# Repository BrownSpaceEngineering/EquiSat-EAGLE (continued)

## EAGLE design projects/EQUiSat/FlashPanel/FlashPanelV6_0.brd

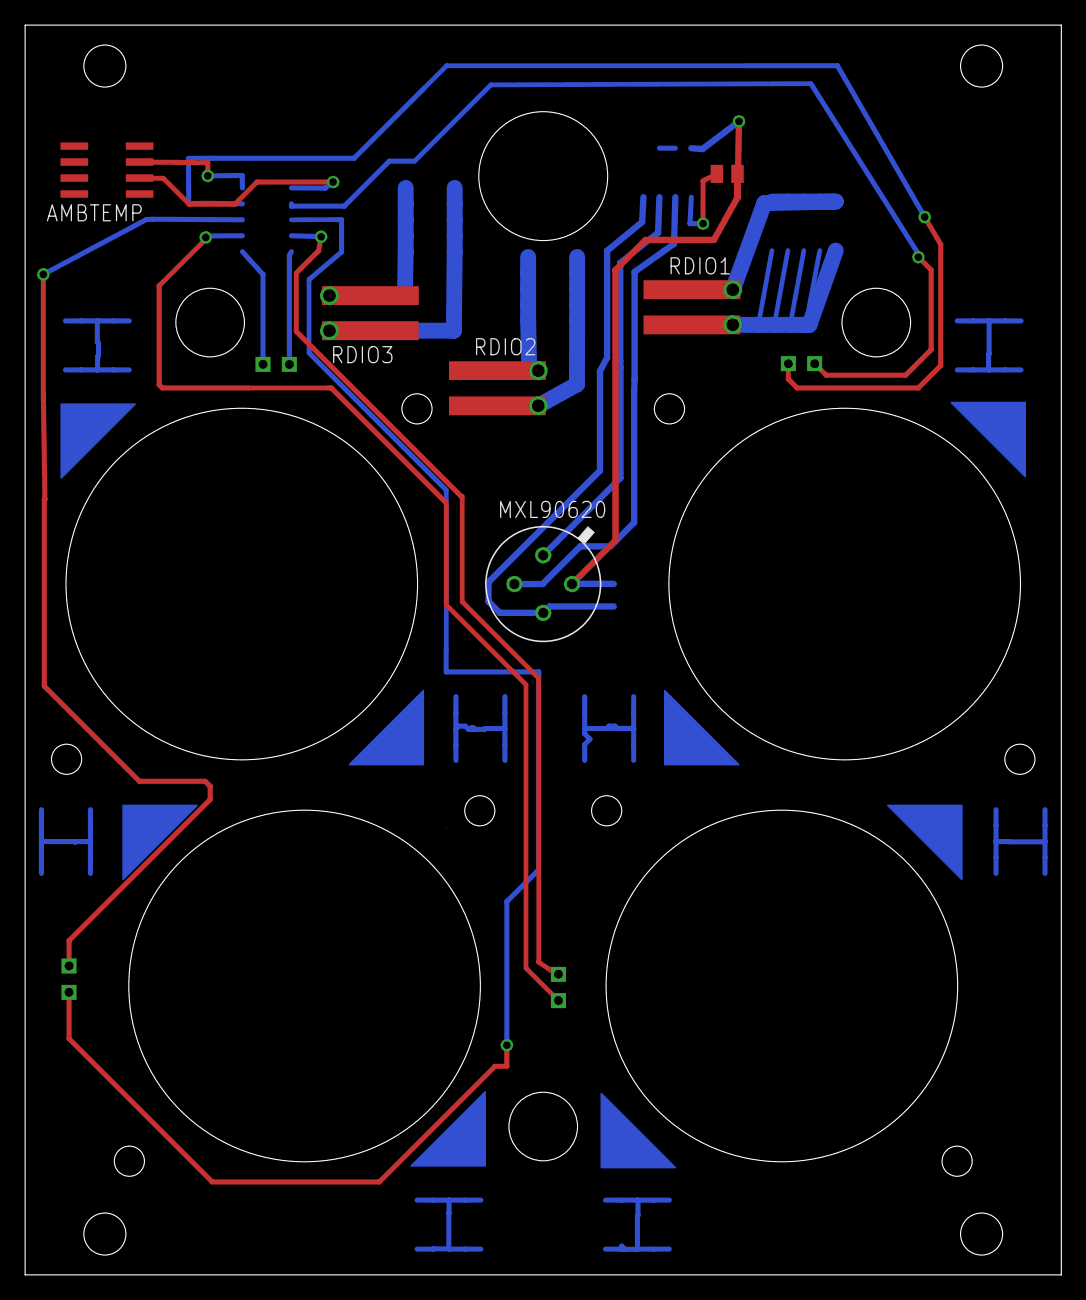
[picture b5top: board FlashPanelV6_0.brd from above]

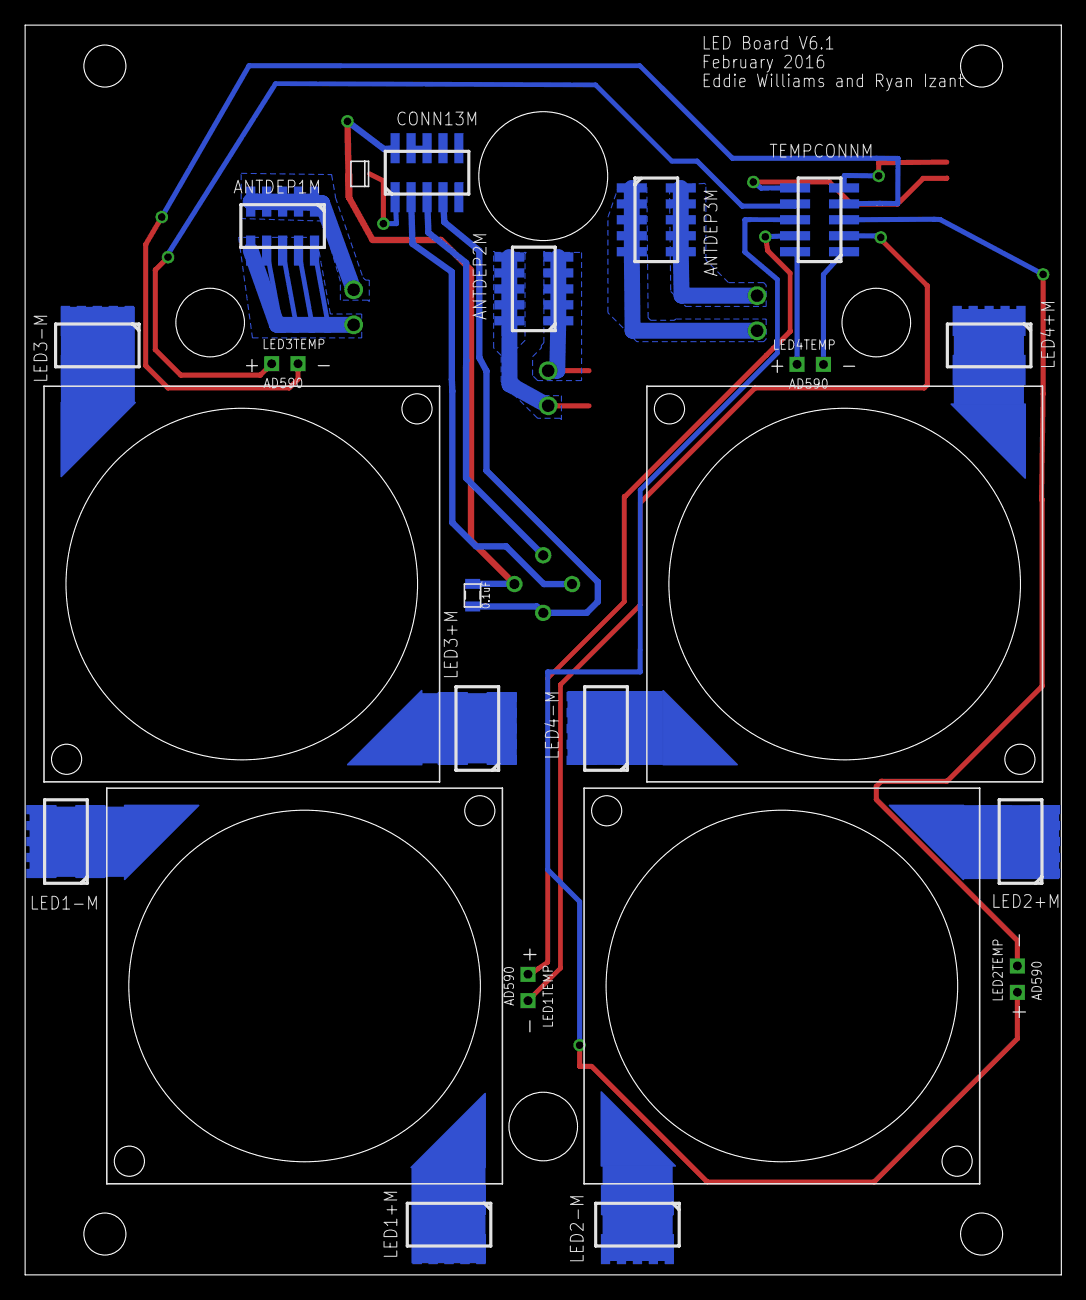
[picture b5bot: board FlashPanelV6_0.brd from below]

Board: 2 copper layers, 82.5 x 99.5 mm, 28 parts (26 on the bottom side), 30 nets.

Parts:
AMBTEMP: AD590; 8SOIC
ANTDEP1M, ANTDEP2M, ANTDEP3M: 10PINMALE
C1: 0.1uF; 0805
CONN13M: 10PINMALE
LED1, LED2, LED3, LED4: CXM27
LED1+M, LED1-M, LED2+M, LED2-M, LED3+M, LED3-M, LED4+M, LED4-M: 10PINMALE
LED1TEMP, LED2TEMP, LED3TEMP, LED4TEMP: AD590-TH; AD590TH
RDIO1, RDIO2, RDIO3: RDIO; RDIO_DPLY
TEMPCONNM: 10PINMALE
U$1: MXL90620
U$2: PHOTODETECTBOTTOM

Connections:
3V3: C1.2, CONN13M.P4, U$1.VDD
GND: C1.1, CONN13M.P10, U$1.VSS, U$2.GND
unnamed: LED3.ANODE, LED3+M.P1, LED3+M.P2, LED3+M.P3, LED3+M.P4, LED3+M.P5, LED3+M.P6, LED3+M.P7, LED3+M.P8, LED3+M.P9, LED3+M.P10
unnamed: LED3.CATHODE, LED3-M.P1, LED3-M.P2, LED3-M.P3, LED3-M.P4, LED3-M.P5, LED3-M.P6, LED3-M.P7, LED3-M.P8, LED3-M.P9, LED3-M.P10
unnamed: LED2.CATHODE, LED2+M.P1, LED2+M.P2, LED2+M.P3, LED2+M.P4, LED2+M.P5, LED2+M.P6, LED2+M.P7, LED2+M.P8, LED2+M.P9, LED2+M.P10
unnamed: LED2.ANODE, LED2-M.P1, LED2-M.P2, LED2-M.P3, LED2-M.P4, LED2-M.P5, LED2-M.P6, LED2-M.P7, LED2-M.P8, LED2-M.P9, LED2-M.P10
unnamed: LED1.CATHODE, LED1+M.P1, LED1+M.P2, LED1+M.P3, LED1+M.P4, LED1+M.P5, LED1+M.P6, LED1+M.P7, LED1+M.P8, LED1+M.P9, LED1+M.P10
unnamed: LED1.ANODE, LED1-M.P1, LED1-M.P2, LED1-M.P3, LED1-M.P4, LED1-M.P5, LED1-M.P6, LED1-M.P7, LED1-M.P8, LED1-M.P9, LED1-M.P10
unnamed: LED4.CATHODE, LED4-M.P1, LED4-M.P2, LED4-M.P3, LED4-M.P4, LED4-M.P5, LED4-M.P6, LED4-M.P7, LED4-M.P8, LED4-M.P9, LED4-M.P10
unnamed: LED4.ANODE, LED4+M.P1, LED4+M.P2, LED4+M.P3, LED4+M.P4, LED4+M.P5, LED4+M.P6, LED4+M.P7, LED4+M.P8, LED4+M.P9, LED4+M.P10
unnamed: ANTDEP1M.P1, ANTDEP1M.P2, ANTDEP1M.P3, ANTDEP1M.P4, ANTDEP1M.P5, RDIO1.P3, RDIO1.P4
unnamed: ANTDEP2M.P6, ANTDEP2M.P7, ANTDEP2M.P8, ANTDEP2M.P9, ANTDEP2M.P10, RDIO2.P1, RDIO2.P2
unnamed: ANTDEP2M.P1, ANTDEP2M.P2, ANTDEP2M.P3, ANTDEP2M.P4, ANTDEP2M.P5, RDIO2.P3, RDIO2.P4
unnamed: ANTDEP3M.P6, ANTDEP3M.P7, ANTDEP3M.P8, ANTDEP3M.P9, ANTDEP3M.P10, RDIO3.P1, RDIO3.P2
unnamed: ANTDEP3M.P1, ANTDEP3M.P2, ANTDEP3M.P3, ANTDEP3M.P4, ANTDEP3M.P5, RDIO3.P3, RDIO3.P4
unnamed: LED4TEMP.P$2, TEMPCONNM.P1
unnamed: LED1TEMP.P$2, TEMPCONNM.P2
unnamed: LED2TEMP.P$2, TEMPCONNM.P3
unnamed: LED3TEMP.P$2, TEMPCONNM.P4
unnamed: LED4TEMP.P$1, TEMPCONNM.P10
unnamed: LED1TEMP.P$1, TEMPCONNM.P9
unnamed: LED2TEMP.P$1, TEMPCONNM.P8
unnamed: LED3TEMP.P$1, TEMPCONNM.P7
unnamed: AMBTEMP.3, TEMPCONNM.P5
unnamed: AMBTEMP.2, TEMPCONNM.P6
PDOUT: CONN13M.P1, U$2.PWROUT
RDIO1: ANTDEP1M.P6, ANTDEP1M.P7, ANTDEP1M.P8, ANTDEP1M.P9, ANTDEP1M.P10, RDIO1.P1, RDIO1.P2
SCL: CONN13M.P3, U$1.SCL
SDA: CONN13M.P2, U$1.SDA
TEST: CONN13M.P8, CONN13M.P9

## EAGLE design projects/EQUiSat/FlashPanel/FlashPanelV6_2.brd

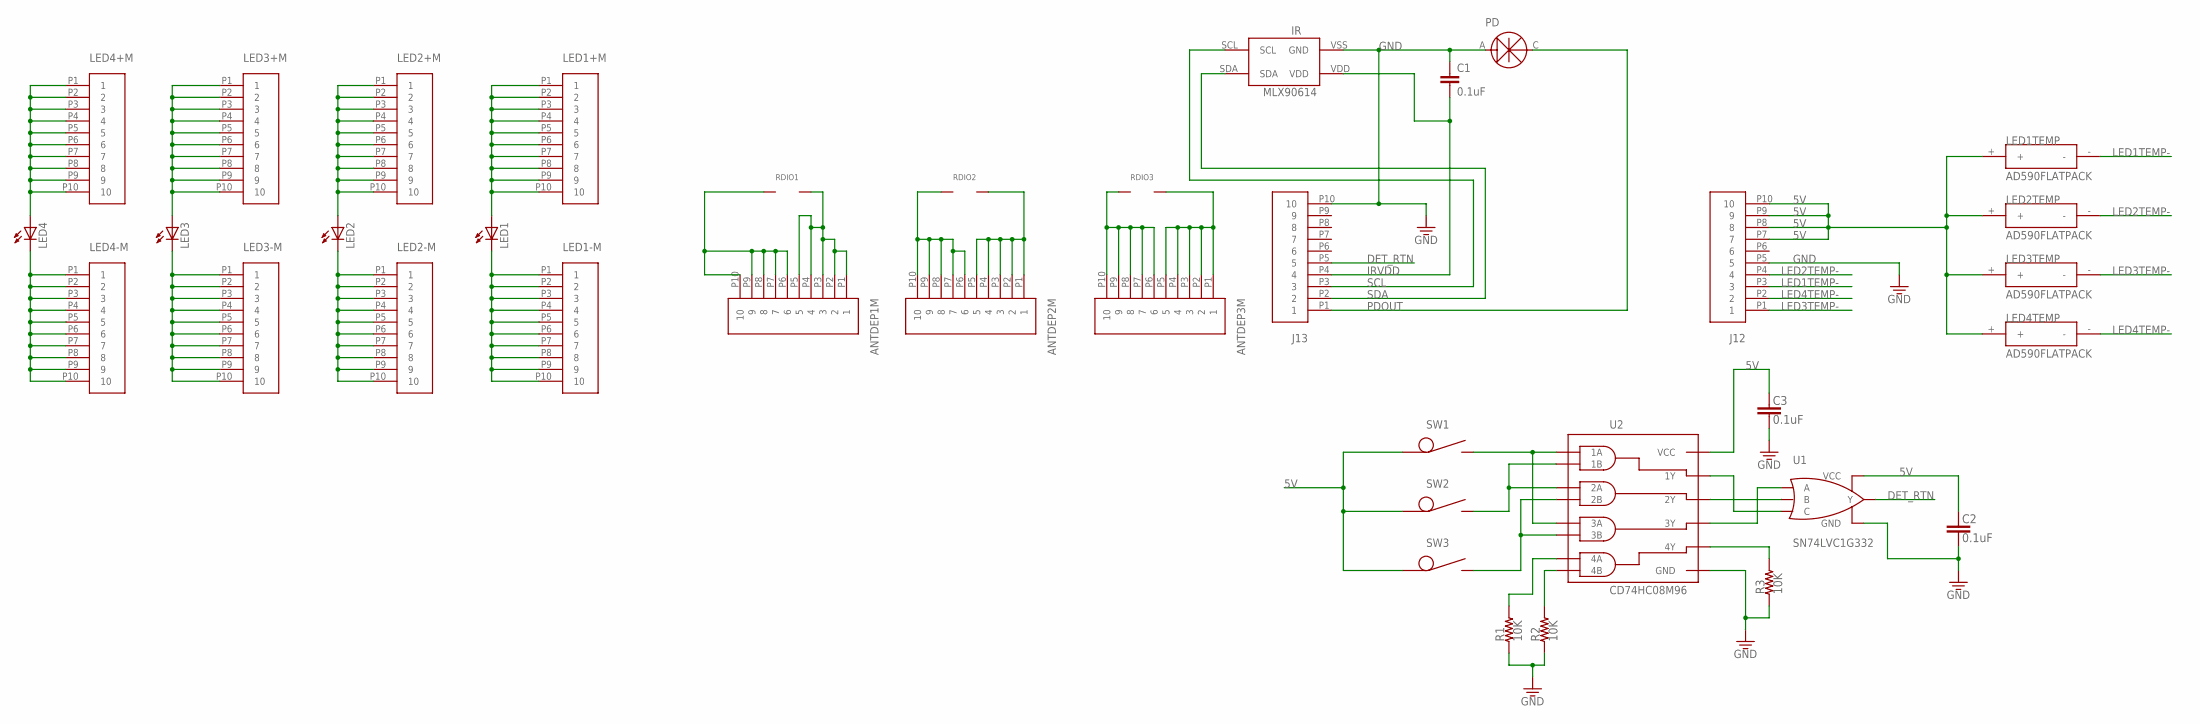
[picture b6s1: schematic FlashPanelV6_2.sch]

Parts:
ANTDEP1M, ANTDEP2M, ANTDEP3M: 10PINMALE
C1, C2, C3: 0.1uF; 0805
IR: MXL90614; MXL90620
J12, J13: 10PINMALE
LED1, LED2, LED3, LED4: CXM27
LED1+M, LED1-M, LED2+M, LED2-M, LED3+M, LED3-M, LED4+M, LED4-M: 10PINMALE
LED1TEMP, LED2TEMP, LED3TEMP, LED4TEMP: AD590FLATPACK; FLATPACK
PD: TEMD6200
R1, R2, R3: 10K; 0805
RDIO1, RDIO2, RDIO3: RDIO; RDIO_DPLY
SW1, SW2, SW3: SW-DETECT; SW-SPRING
U1: SN74LVC1G332; DCK-6
U2: CD74HC08M96; SOIC-14

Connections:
5V: C2.1, C3.1, J12.P7 (7), J12.P8 (8), J12.P9 (9), J12.P10 (10), LED1TEMP.+, LED2TEMP.+, LED3TEMP.+, LED4TEMP.+, SW1.P$1, SW2.P$1, SW3.P$1, U1.P$5 (VCC), U2.P$14 (VCC)
DET_RTN: J13.P5 (5), U1.P$4 (Y)
GND: C1.1, C2.2, C3.2, IR.VSS (GND), J12.P5 (5), J13.P10 (10), PD.A, R1.1, R2.1, R3.1, U1.P$2 (GND), U2.P$7 (GND)
IRVDD: C1.2, IR.VDD, J13.P4 (4)
LED1M: LED1.CATHODE (C), LED1-M.P1 (1), LED1-M.P2 (2), LED1-M.P3 (3), LED1-M.P4 (4), LED1-M.P5 (5), LED1-M.P6 (6), LED1-M.P7 (7), LED1-M.P8 (8), LED1-M.P9 (9), LED1-M.P10 (10)
LED1P: LED1.ANODE (A), LED1+M.P1 (1), LED1+M.P2 (2), LED1+M.P3 (3), LED1+M.P4 (4), LED1+M.P5 (5), LED1+M.P6 (6), LED1+M.P7 (7), LED1+M.P8 (8), LED1+M.P9 (9), LED1+M.P10 (10)
LED1TEMP-: J12.P3 (3), LED1TEMP.-
LED2M: LED2.CATHODE (C), LED2-M.P1 (1), LED2-M.P2 (2), LED2-M.P3 (3), LED2-M.P4 (4), LED2-M.P5 (5), LED2-M.P6 (6), LED2-M.P7 (7), LED2-M.P8 (8), LED2-M.P9 (9), LED2-M.P10 (10)
LED2P: LED2.ANODE (A), LED2+M.P1 (1), LED2+M.P2 (2), LED2+M.P3 (3), LED2+M.P4 (4), LED2+M.P5 (5), LED2+M.P6 (6), LED2+M.P7 (7), LED2+M.P8 (8), LED2+M.P9 (9), LED2+M.P10 (10)
LED2TEMP-: J12.P4 (4), LED2TEMP.-
LED3M: LED3.CATHODE (C), LED3-M.P1 (1), LED3-M.P2 (2), LED3-M.P3 (3), LED3-M.P4 (4), LED3-M.P5 (5), LED3-M.P6 (6), LED3-M.P7 (7), LED3-M.P8 (8), LED3-M.P9 (9), LED3-M.P10 (10)
LED3P: LED3.ANODE (A), LED3+M.P1 (1), LED3+M.P2 (2), LED3+M.P3 (3), LED3+M.P4 (4), LED3+M.P5 (5), LED3+M.P6 (6), LED3+M.P7 (7), LED3+M.P8 (8), LED3+M.P9 (9), LED3+M.P10 (10)
LED3TEMP-: J12.P1 (1), LED3TEMP.-
LED4M: LED4.CATHODE (C), LED4-M.P1 (1), LED4-M.P2 (2), LED4-M.P3 (3), LED4-M.P4 (4), LED4-M.P5 (5), LED4-M.P6 (6), LED4-M.P7 (7), LED4-M.P8 (8), LED4-M.P9 (9), LED4-M.P10 (10)
LED4P: LED4.ANODE (A), LED4+M.P1 (1), LED4+M.P2 (2), LED4+M.P3 (3), LED4+M.P4 (4), LED4+M.P5 (5), LED4+M.P6 (6), LED4+M.P7 (7), LED4+M.P8 (8), LED4+M.P9 (9), LED4+M.P10 (10)
LED4TEMP-: J12.P2 (2), LED4TEMP.-
unnamed: U1.P$6 (C), U2.P$3 (1Y)
unnamed: U1.P$3 (B), U2.P$6 (2Y)
unnamed: U1.P$1 (A), U2.P$8 (3Y)
unnamed: SW1.P$2, U2.P$1 (1A), U2.P$9 (3A)
unnamed: SW2.P$2, U2.P$2 (1B), U2.P$4 (2A)
unnamed: SW3.P$2, U2.P$5 (2B), U2.P$10 (3B)
unnamed: R2.2, U2.P$13 (4B)
unnamed: R1.2, U2.P$12 (4A)
unnamed: R3.2, U2.P$11 (4Y)
PDOUT: J13.P1 (1), PD.C
RDIO1+: ANTDEP1M.P6 (6), ANTDEP1M.P7 (7), ANTDEP1M.P8 (8), ANTDEP1M.P9 (9), ANTDEP1M.P10 (10), RDIO1.P3, RDIO1.P4
RDIO1-: ANTDEP1M.P1 (1), ANTDEP1M.P2 (2), ANTDEP1M.P3 (3), ANTDEP1M.P4 (4), ANTDEP1M.P5 (5), RDIO1.P1, RDIO1.P2
RDIO2+: ANTDEP2M.P6 (6), ANTDEP2M.P7 (7), ANTDEP2M.P8 (8), ANTDEP2M.P9 (9), ANTDEP2M.P10 (10), RDIO2.P3, RDIO2.P4
RDIO2-: ANTDEP2M.P1 (1), ANTDEP2M.P2 (2), ANTDEP2M.P3 (3), ANTDEP2M.P4 (4), ANTDEP2M.P5 (5), RDIO2.P1, RDIO2.P2
RDIO3+: ANTDEP3M.P6 (6), ANTDEP3M.P7 (7), ANTDEP3M.P8 (8), ANTDEP3M.P9 (9), ANTDEP3M.P10 (10), RDIO3.P3, RDIO3.P4
RDIO3-: ANTDEP3M.P1 (1), ANTDEP3M.P2 (2), ANTDEP3M.P3 (3), ANTDEP3M.P4 (4), ANTDEP3M.P5 (5), RDIO3.P1, RDIO3.P2
SCL: IR.SCL, J13.P3 (3)
SDA: IR.SDA, J13.P2 (2)

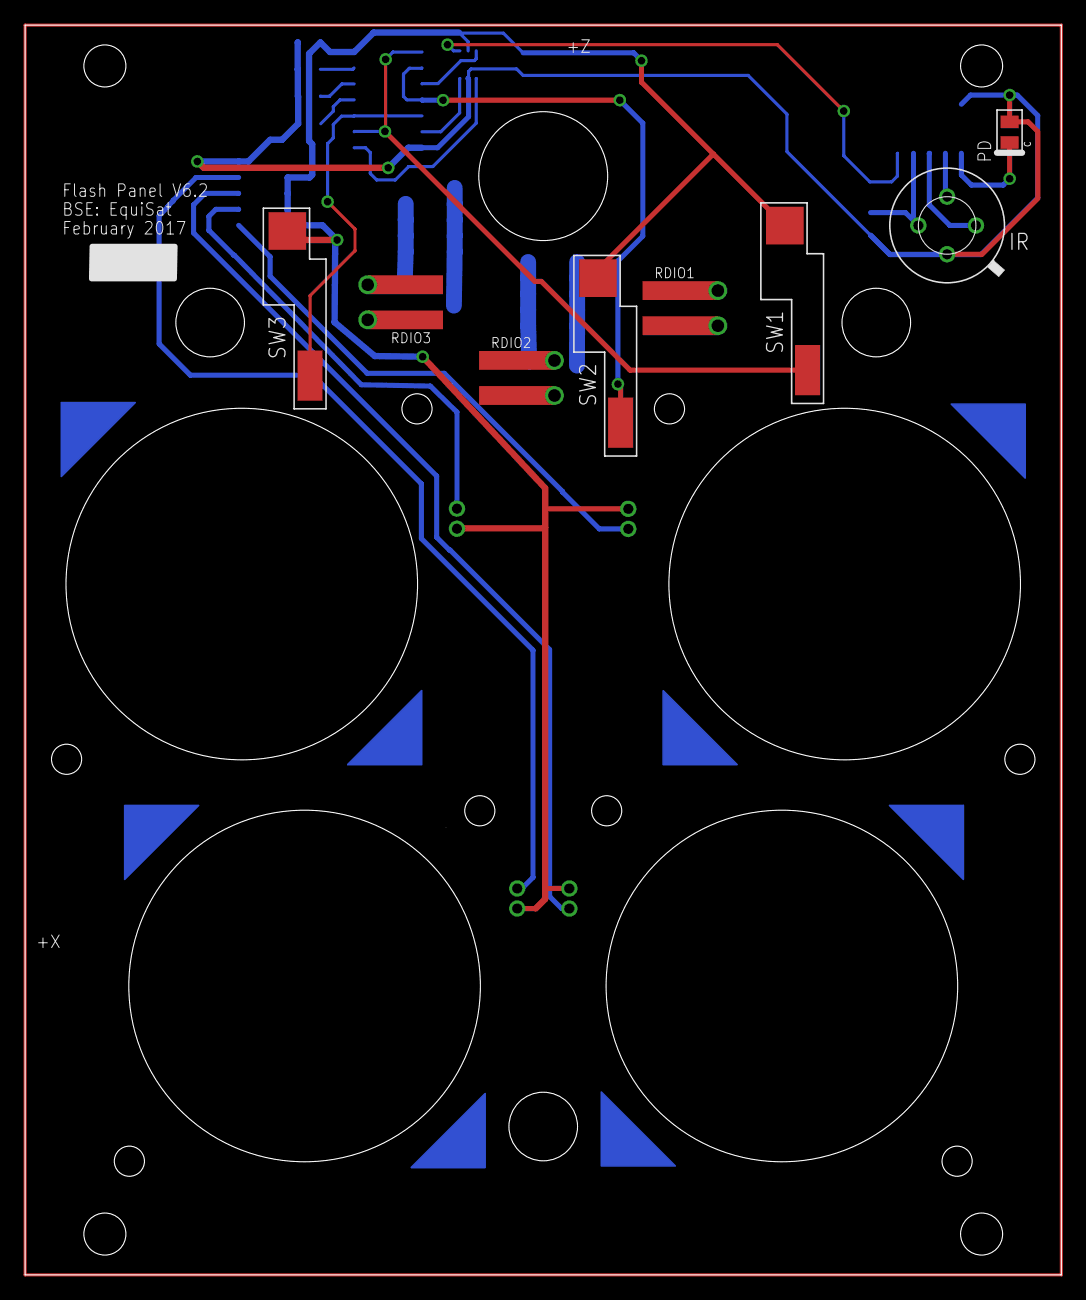
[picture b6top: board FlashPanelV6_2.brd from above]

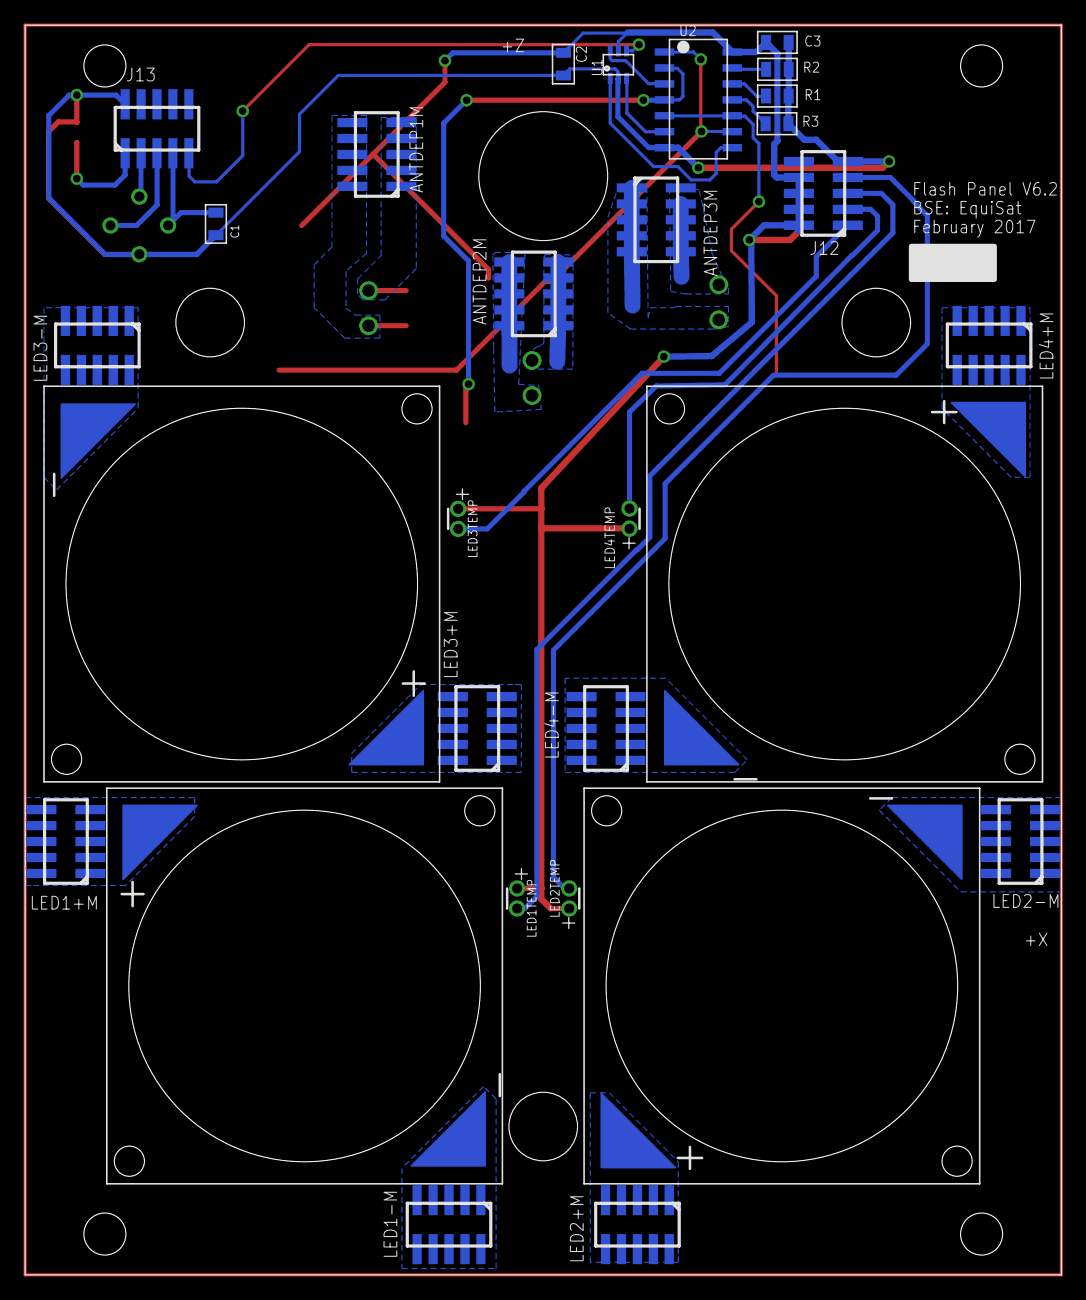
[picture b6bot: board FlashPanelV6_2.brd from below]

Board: 2 copper layers, 82.5 x 99.5 mm, 37 parts (25 on the bottom side), 34 nets.

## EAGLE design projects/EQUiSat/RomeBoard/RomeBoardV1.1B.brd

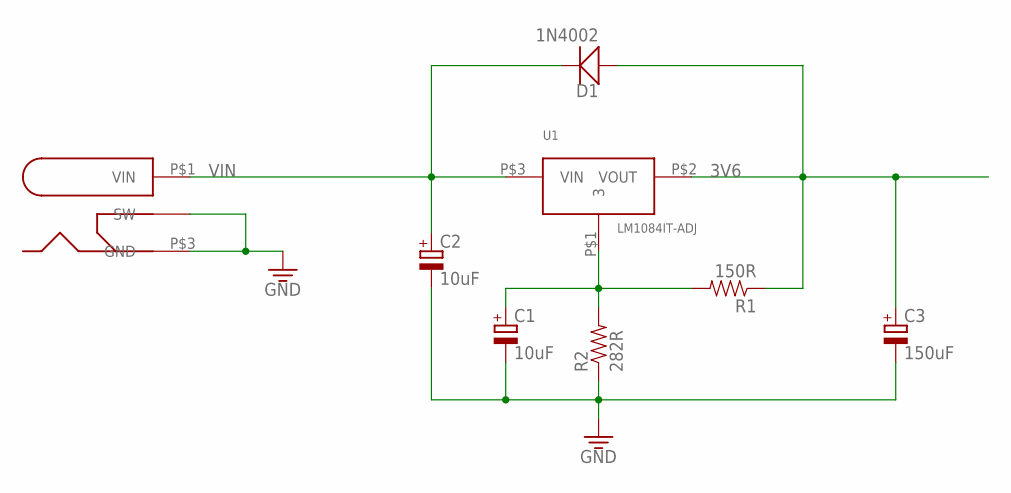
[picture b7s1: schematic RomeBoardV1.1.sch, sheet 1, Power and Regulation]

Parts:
C1, C2: 10uF; E2,5-7
C3: 150uF; E5-13
D1: 1N4002; DO-201AD
R1: 150R; AXIAL-0.4
R2: 282R; AXIAL-0.4
U1: LM1084IT-ADJ; TO-220-507302B00000G
U$2: PJ-002A

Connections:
3V6: C3.+, D1.P$1 (A), R1.1, U1.P$2 (VOUT); also elsewhere on the board
GND: C1.-, C2.-, C3.-, R2.1, U$2.P$2 (SW), U$2.P$3 (GND); also elsewhere on the board
unnamed: C1.+, R1.2, R2.2, U1.P$1 (3)
VIN: C2.+, D1.P$2 (C), U1.P$3 (VIN), U$2.P$1 (VIN); also elsewhere on the board

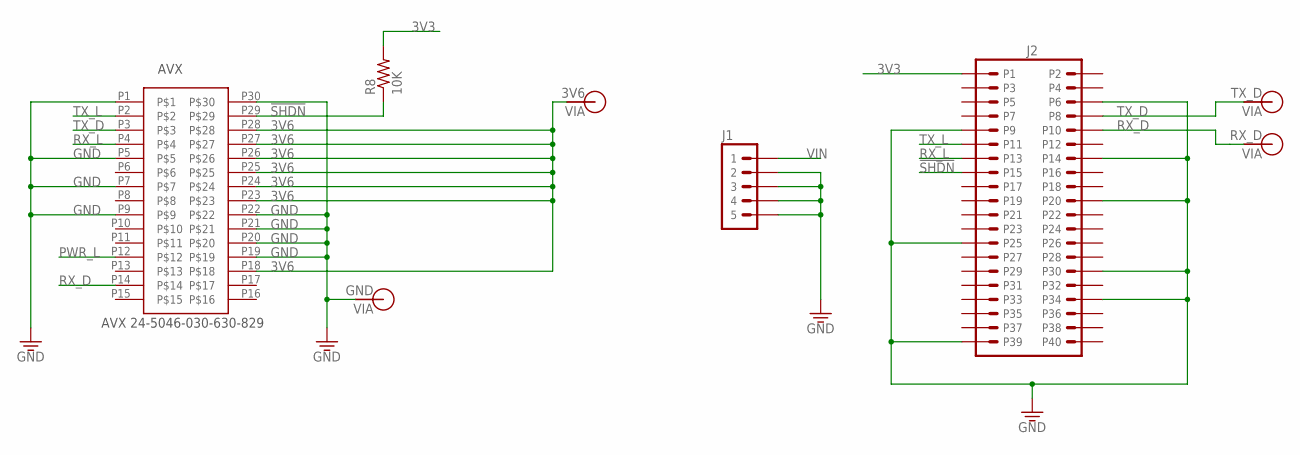
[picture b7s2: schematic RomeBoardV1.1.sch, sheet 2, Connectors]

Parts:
AVX: AVX-24-5046-030-630-829; AVX-24-5046-630-829
J1: HEADER-5; HEADER-05
J2: RASPBERRY-PI-HEADER; HEADER-20X02
R8: 10K; AXIAL-0.4
V1: TX_D; VIA-120MIL
V2: RX_D; VIA-120MIL
V4: GND; VIA-120MIL
V5: 3V6; VIA-120MIL

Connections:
3V3: J2.P1, R8.2; also elsewhere on the board
3V6: AVX.P18, AVX.P23, AVX.P24, AVX.P25, AVX.P26, AVX.P27, AVX.P28, V5.P$1; also elsewhere on the board
!SHDN: AVX.P29, J2.P15, R8.1; also elsewhere on the board
GND: AVX.P1, AVX.P5, AVX.P7, AVX.P9, AVX.P19, AVX.P20, AVX.P21, AVX.P22, AVX.P30, J1.2, J1.3, J1.4, J1.5, J2.P6, J2.P9, J2.P14, J2.P20, J2.P25, J2.P30, J2.P34, J2.P39, V4.P$1; also elsewhere on the board
PWR_L: AVX.P12; also elsewhere on the board
RX_D: AVX.P14, J2.P10, V2.P$1
RX_L: AVX.P4, J2.P13; also elsewhere on the board
TX_D: AVX.P3, J2.P8, V1.P$1
TX_L: AVX.P2, J2.P11; also elsewhere on the board
VIN: J1.1; also elsewhere on the board

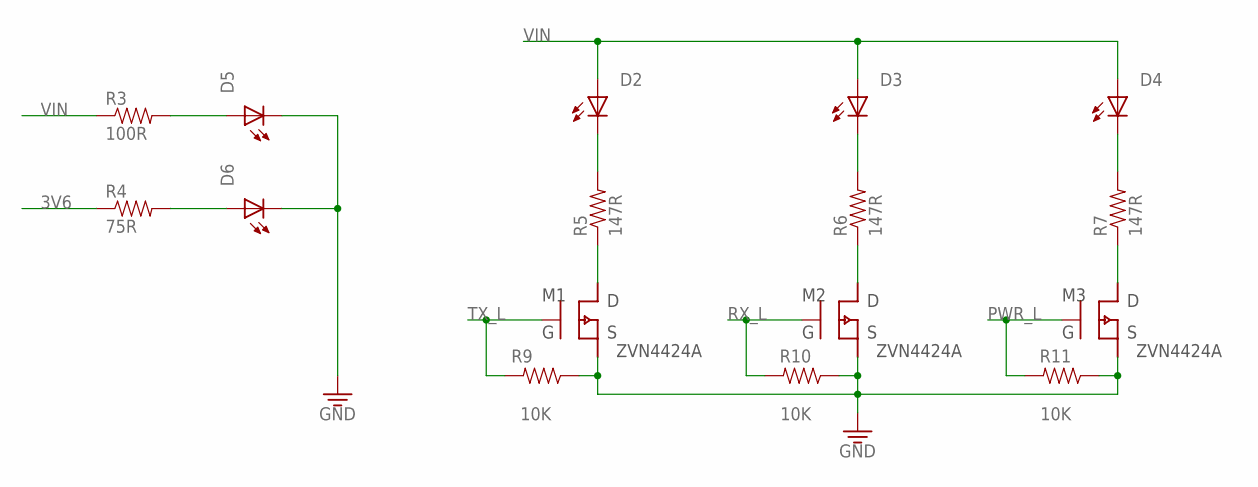
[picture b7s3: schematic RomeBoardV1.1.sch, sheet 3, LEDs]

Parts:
D2, D3, D4, D5, D6: LEDTHRU-HOLE-CONNECTOR; 1X2-POL
M1, M2, M3: ZVN4424A; TO-923-MOS
R3: 100R; AXIAL-0.4
R4: 75R; AXIAL-0.4
R5, R6, R7: 147R; AXIAL-0.4
R9, R10, R11: 10K; AXIAL-0.4

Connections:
3V6: R4.1; also elsewhere on the board
GND: D5.2 (C), D6.2 (C), M1.3 (S), M2.3 (S), M3.3 (S), R9.1, R10.1, R11.1; also elsewhere on the board
unnamed: D5.1 (A), R3.2
unnamed: D6.1 (A), R4.2
unnamed: D3.2 (C), R6.2
unnamed: M1.1 (D), R5.1
unnamed: M2.1 (D), R6.1
unnamed: M3.1 (D), R7.1
unnamed: D4.2 (C), R7.2
unnamed: D2.2 (C), R5.2
PWR_L: M3.2 (G), R11.2; also elsewhere on the board
RX_L: M2.2 (G), R10.2; also elsewhere on the board
TX_L: M1.2 (G), R9.2; also elsewhere on the board
VIN: D2.1 (A), D3.1 (A), D4.1 (A), R3.1; also elsewhere on the board

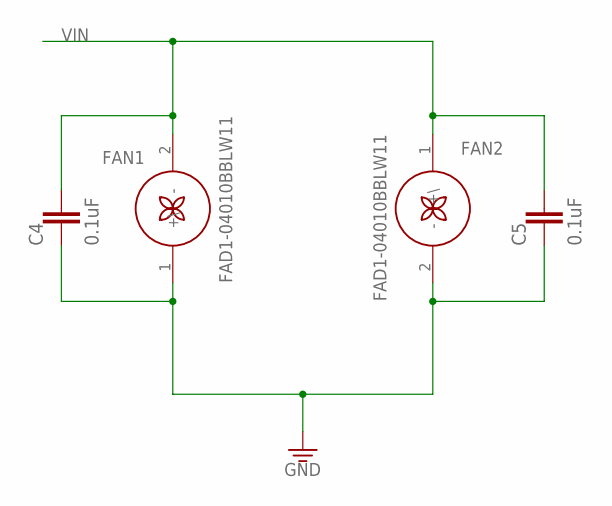
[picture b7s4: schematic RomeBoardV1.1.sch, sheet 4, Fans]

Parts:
C4, C5: 0.1uF; C050-025X075
FAN1, FAN2: FAD1-04010BBLW11; 1X2-POL

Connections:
GND: C4.2, C5.2, FAN1.1 (+\), FAN2.2 (-); also elsewhere on the board
VIN: C4.1, C5.1, FAN1.2 (-), FAN2.1 (+\); also elsewhere on the board

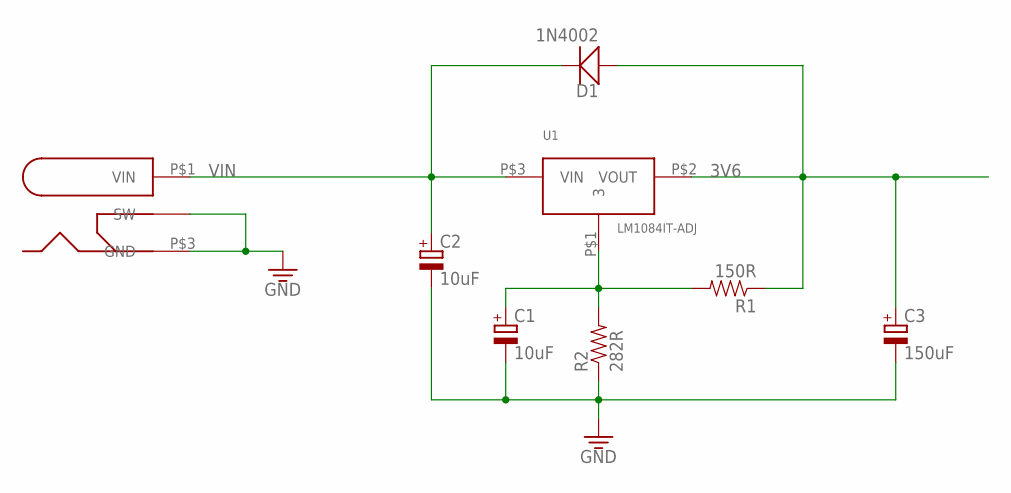
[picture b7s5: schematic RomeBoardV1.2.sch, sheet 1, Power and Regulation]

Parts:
C1, C2: 10uF; E2,5-7
C3: 150uF; E5-13
D1: 1N4002; DO-201AD
R1: 150R; AXIAL-0.4
R2: 282R; AXIAL-0.4
U1: LM1084IT-ADJ; TO-220-507302B00000G
U$2: PJ-002A

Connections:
3V6: C3.+, D1.P$1 (A), R1.1, U1.P$2 (VOUT); also elsewhere on the board
GND: C1.-, C2.-, C3.-, R2.1, U$2.P$2 (SW), U$2.P$3 (GND); also elsewhere on the board
unnamed: C1.+, R1.2, R2.2, U1.P$1 (3)
VIN: C2.+, D1.P$2 (C), U1.P$3 (VIN), U$2.P$1 (VIN); also elsewhere on the board

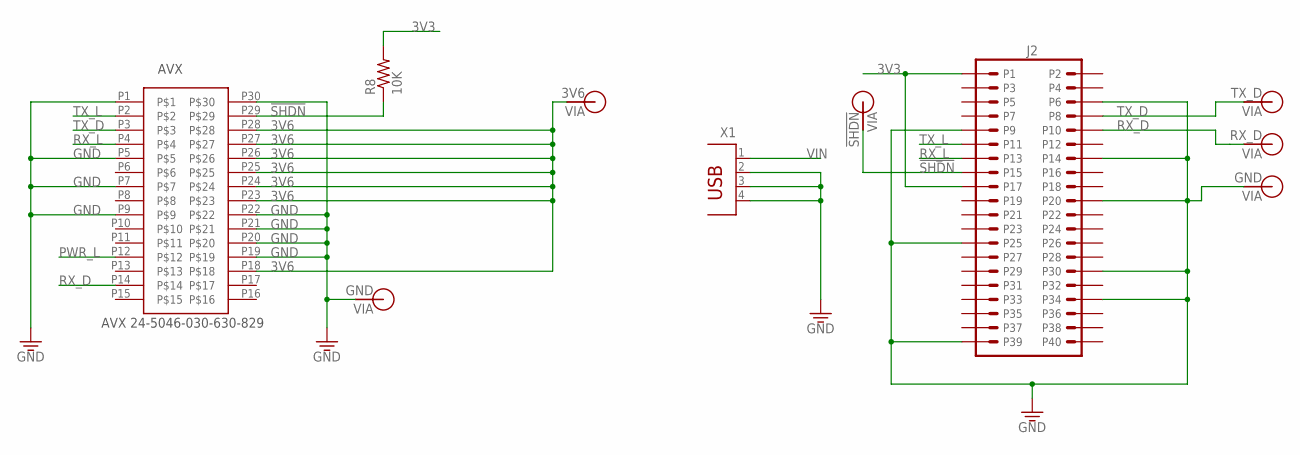
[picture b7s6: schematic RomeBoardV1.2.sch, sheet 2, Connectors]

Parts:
AVX: AVX-24-5046-030-630-829; AVX-24-5046-630-829
J2: RASPBERRY-PI-HEADER; HEADER-20X02
R8: 10K; AXIAL-0.4
V1: TX_D; VIA-60MIL
V2: RX_D; VIA-60MIL
V3: GND; VIA-60MIL
V4: GND; VIA-120MIL
V5: 3V6; VIA-120MIL
V6: !SHDN; VIA-60MIL
X1: PN87520

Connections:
3V3: J2.P1, J2.P17, R8.2
3V6: AVX.P18, AVX.P23, AVX.P24, AVX.P25, AVX.P26, AVX.P27, AVX.P28, V5.P$1; also elsewhere on the board
!SHDN: AVX.P29, J2.P15, R8.1, V6.P$1
GND: AVX.P1, AVX.P5, AVX.P7, AVX.P9, AVX.P19, AVX.P20, AVX.P21, AVX.P22, AVX.P30, J2.P6, J2.P9, J2.P14, J2.P20, J2.P25, J2.P30, J2.P34, J2.P39, V3.P$1, V4.P$1, X1.2, X1.3, X1.4; also elsewhere on the board
PWR_L: AVX.P12; also elsewhere on the board
RX_D: AVX.P14, J2.P10, V2.P$1
RX_L: AVX.P4, J2.P13; also elsewhere on the board
TX_D: AVX.P3, J2.P8, V1.P$1
TX_L: AVX.P2, J2.P11; also elsewhere on the board

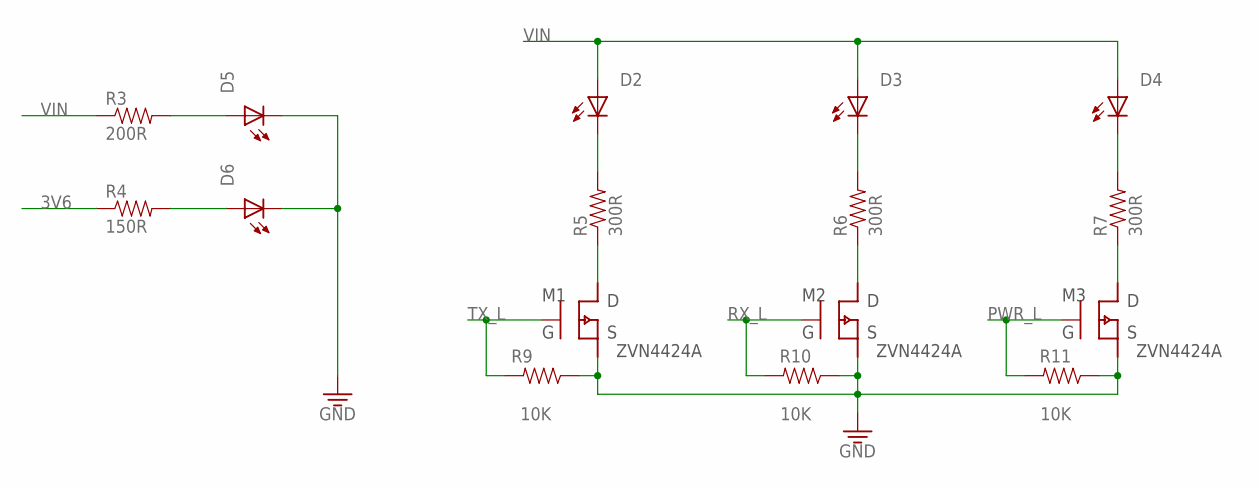
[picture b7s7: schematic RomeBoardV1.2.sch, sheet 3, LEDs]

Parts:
D2, D3, D4, D5, D6: LEDTHRU-HOLE-CONNECTOR; 1X2-POL
M1, M2, M3: ZVN4424A; TO-923-MOS
R3: 200R; AXIAL-0.4
R4: 150R; AXIAL-0.4
R5, R6, R7: 300R; AXIAL-0.4
R9, R10, R11: 10K; AXIAL-0.4

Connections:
3V6: R4.1; also elsewhere on the board
GND: D5.2 (C), D6.2 (C), M1.3 (S), M2.3 (S), M3.3 (S), R9.1, R10.1, R11.1; also elsewhere on the board
unnamed: D5.1 (A), R3.2
unnamed: D6.1 (A), R4.2
unnamed: D3.2 (C), R6.2
unnamed: M1.1 (D), R5.1
unnamed: M2.1 (D), R6.1
unnamed: M3.1 (D), R7.1
unnamed: D4.2 (C), R7.2
unnamed: D2.2 (C), R5.2
PWR_L: M3.2 (G), R11.2; also elsewhere on the board
RX_L: M2.2 (G), R10.2; also elsewhere on the board
TX_L: M1.2 (G), R9.2; also elsewhere on the board
VIN: D2.1 (A), D3.1 (A), D4.1 (A), R3.1; also elsewhere on the board

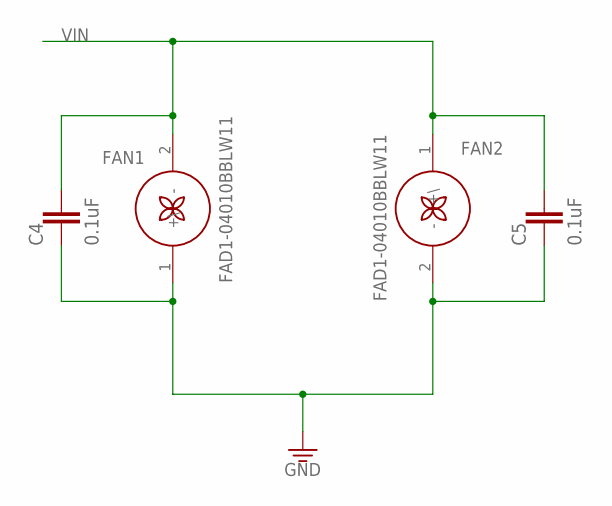
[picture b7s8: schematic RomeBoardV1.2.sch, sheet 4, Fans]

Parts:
C4, C5: 0.1uF; C050-025X075
FAN1, FAN2: FAD1-04010BBLW11; 1X2-POL

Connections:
GND: C4.2, C5.2, FAN1.1 (+\), FAN2.2 (-); also elsewhere on the board
VIN: C4.1, C5.1, FAN1.2 (-), FAN2.1 (+\); also elsewhere on the board

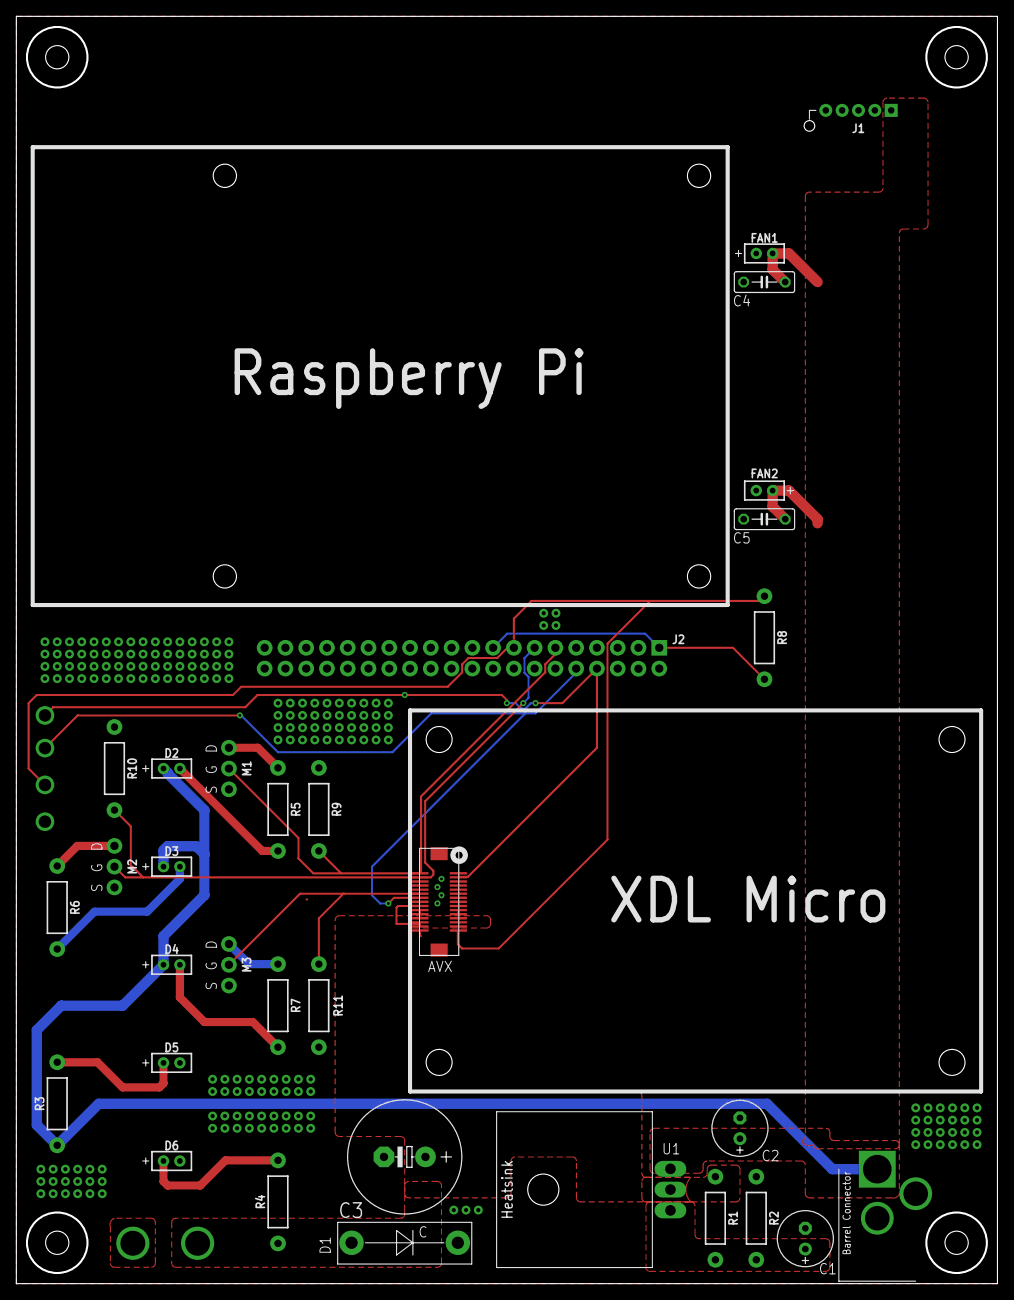
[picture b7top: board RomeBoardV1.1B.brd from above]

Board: 2 copper layers, 120.0 x 155.0 mm, 38 parts (0 on the bottom side), 19 nets.
